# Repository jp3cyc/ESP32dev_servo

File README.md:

# ESP32dev_servo
 esp32 and neopixcel

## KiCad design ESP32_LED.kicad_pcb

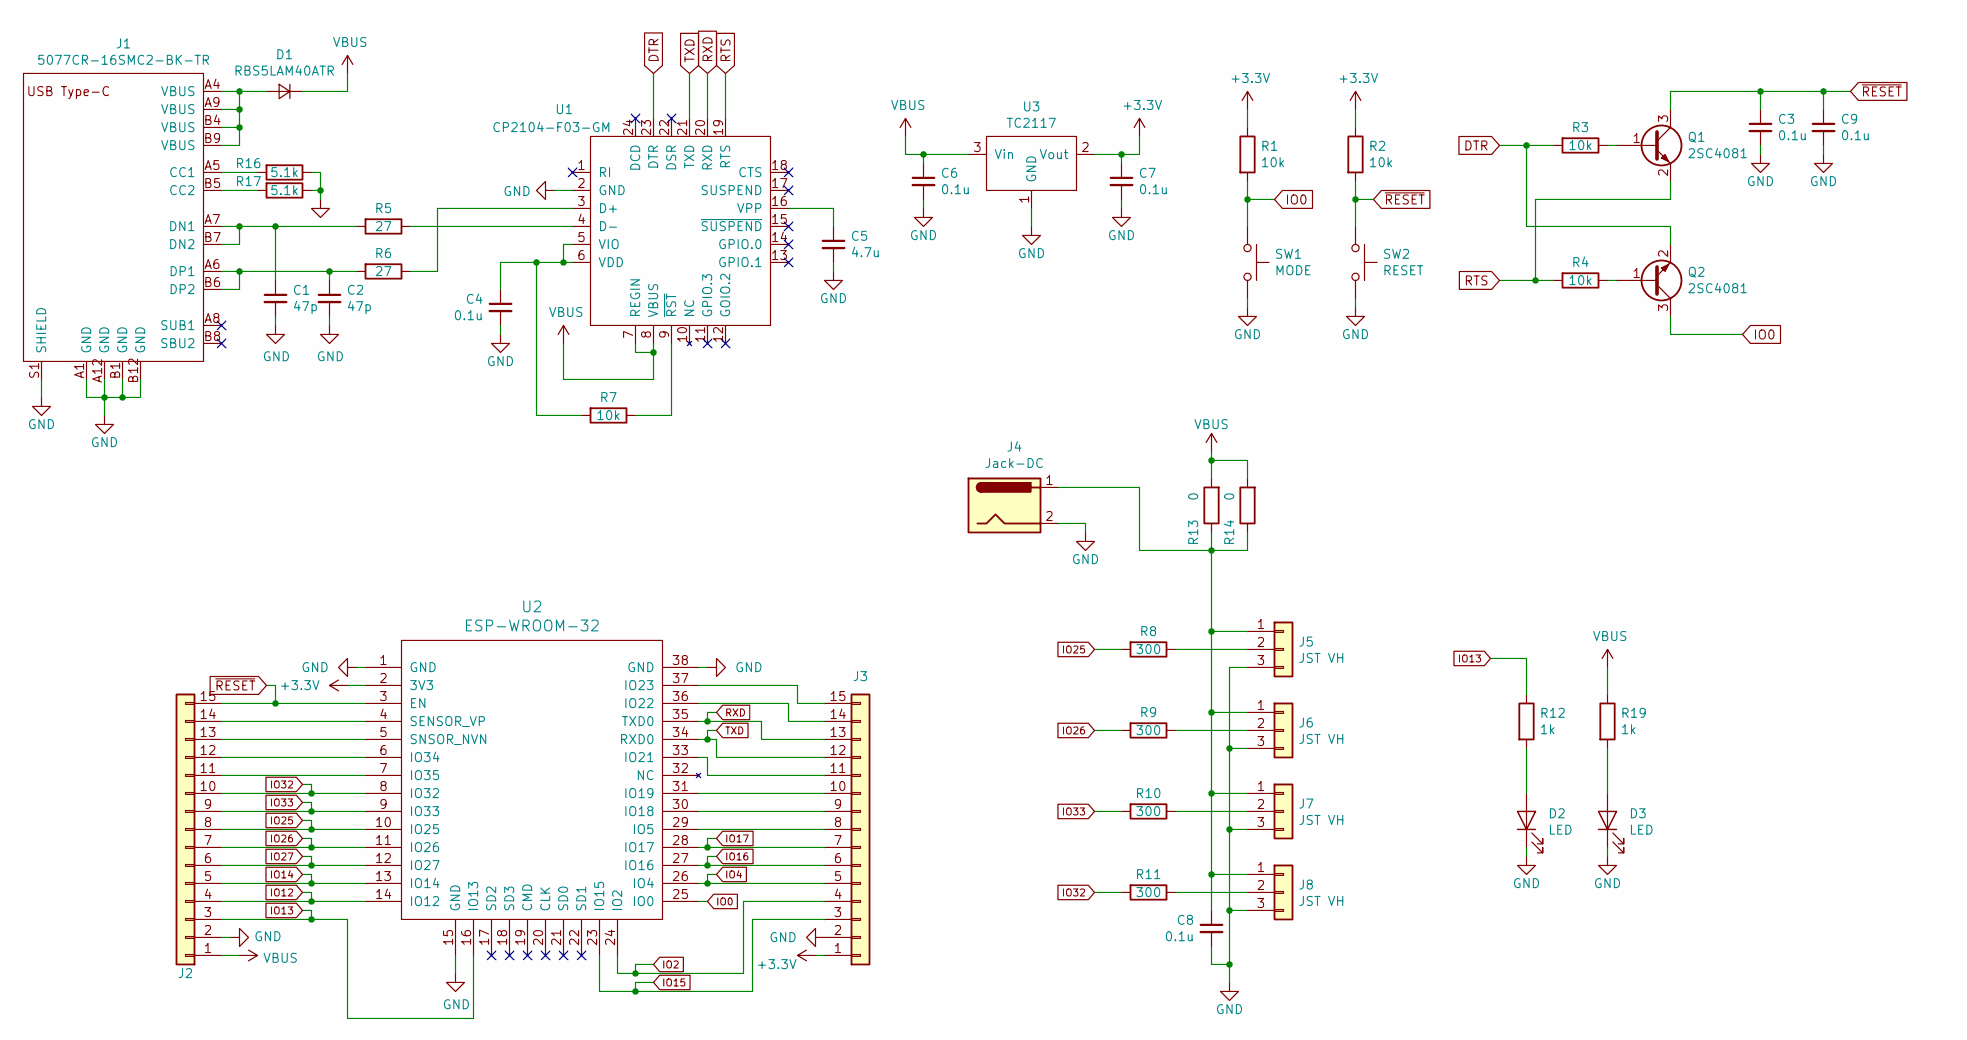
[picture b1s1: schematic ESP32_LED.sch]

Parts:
C1, C2: 47p; C_0402_1005Metric
C3, C4, C6, C7, C8, C9: 0.1u; C_0402_1005Metric
C5: 4.7u; C_0603_1608Metric
D1: RBS5LAM40ATR; SOD-128
D2, D3: LED; LED_0402_1005Metric
J1: 5077CR-16SMC2-BK-TR
J2, J3: Conn_01x15; PinHeader_1x15_P2.54mm_Vertical
J4: Jack-DC; 2DC-G213-D42
J5, J6, J7, J8: JST VH; JST_VH_B3P-VH-B_1x03_P3.96mm_Vertical
Q1, Q2: 2SC4081; SOT-323_SC-70
R1, R2, R3, R4, R7: 10k; R_0402_1005Metric
R5, R6: 27; R_0402_1005Metric
R8, R9, R10, R11: 300; R_0402_1005Metric
R12, R19: 1k; R_0402_1005Metric
R13, R14: 0; R_0805_2012Metric
R16, R17: 5.1k; R_0402_1005Metric
SW1: MODE; SKRPACE010
SW2: RESET; SKRPACE010
U1: CP2104-F03-GM; QFN-24-1EP_4x4mm_P0.5mm_EP2.7x2.7mm_ThermalVias
U2: ESP-WROOM-32; ESP32
U3: TC2117; SOT-223

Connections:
+3V3: C7.1, J3.1, R1.1, R2.1, U2.2 (3V3), U3.2 (Vout)
DTR: Q2.2 (E), R3.2, U1.23 (DTR)
GND: C1.2, C2.2, C3.2, C4.2, C5.2, C6.2, C7.2, C8.2, C9.2, D2.1 (K), D3.1 (K), J1.A1 (GND), J1.A12 (GND), J1.B1 (GND), J1.B12 (GND), J1.S1 (SHIELD), J2.2, J3.2, J4.2, J5.3, J6.3, J7.3, J8.3, R16.1, R17.1, SW1.2, SW2.2, U1.2 (GND), U2.1 (GND), U2.15 (GND), U2.38 (GND), U2.GND, U3.1 (GND)
IO0: Q2.3 (C), R1.2, SW1.1, U2.25 (IO0)
IO2: J3.4, U2.24 (IO2)
IO4: J3.5, U2.26 (IO4)
IO12: J2.4, U2.14 (IO12)
IO13: J2.3, R12.1, U2.16 (IO13)
IO14: J2.5, U2.13 (IO14)
IO15: J3.3, U2.23 (IO15)
IO16: J3.6, U2.27 (IO16)
IO17: J3.7, U2.28 (IO17)
IO25: J2.8, R8.2, U2.10 (IO25)
IO26: J2.7, R9.2, U2.11 (IO26)
IO27: J2.6, U2.12 (IO27)
IO32: J2.10, R11.2, U2.8 (IO32)
IO33: J2.9, R10.2, U2.9 (IO33)
unnamed: C1.1, J1.A7 (DN1), J1.B7 (DN2), R5.2
unnamed: C2.1, J1.A6 (DP1), J1.B6 (DP2), R6.2
unnamed: C4.1, R7.2, U1.5 (VIO), U1.6 (VDD)
unnamed: C5.1, U1.16 (VPP)
unnamed: C8.1, J4.1, J5.1, J6.1, J7.1, J8.1, R13.1, R14.1
unnamed: D1.2 (A), J1.A4 (VBUS), J1.A9 (VBUS), J1.B4 (VBUS), J1.B9 (VBUS)
unnamed: D2.2 (A), R12.2
unnamed: D3.2 (A), R19.2
unnamed: J1.A5 (CC1), R16.2
unnamed: J1.B5 (CC2), R17.2
unnamed: J2.11, U2.7 (IO35)
unnamed: J2.12, U2.6 (IO34)
unnamed: J2.13, U2.5 (SNSOR_NVN)
unnamed: J2.14, U2.4 (SENSOR_VP)
unnamed: J3.8, U2.29 (IO5)
unnamed: J3.9, U2.30 (IO18)
unnamed: J3.10, U2.31 (IO19)
unnamed: J3.11, U2.33 (IO21)
unnamed: J3.14, U2.36 (IO22)
unnamed: J3.15, U2.37 (IO23)
unnamed: J5.2, R8.1
unnamed: J6.2, R9.1
unnamed: J7.2, R10.1
unnamed: J8.2, R11.1
unnamed: Q1.1 (B), R3.1
unnamed: Q2.1 (B), R4.1
unnamed: R5.1, U1.4 (D-)
unnamed: R6.1, U1.3 (D+)
unnamed: R7.1, U1.9 (~RST)
RTS: Q1.2 (E), R4.2, U1.19 (RTS)
RXD: J3.13, U1.20 (RXD), U2.35 (TXD0)
TXD: J3.12, U1.21 (TXD), U2.34 (RXD0)
VBUS: C6.1, D1.1 (K), J2.1, R13.2, R14.2, R19.1, U1.7 (REGIN), U1.8 (VBUS), U3.3 (Vin)
~RESET: C3.1, C9.1, J2.15, Q1.3 (C), R2.2, SW2.1, U2.3 (EN)

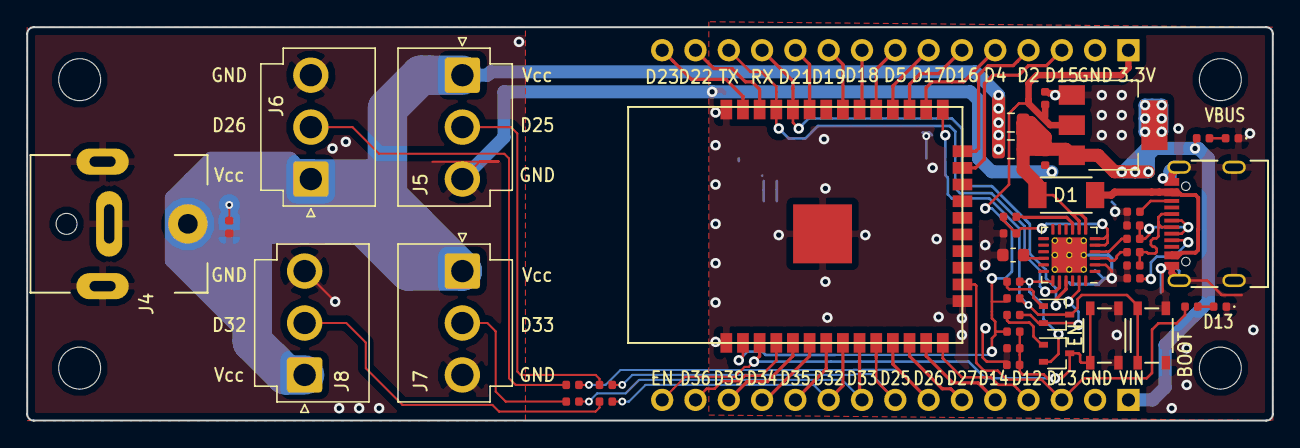
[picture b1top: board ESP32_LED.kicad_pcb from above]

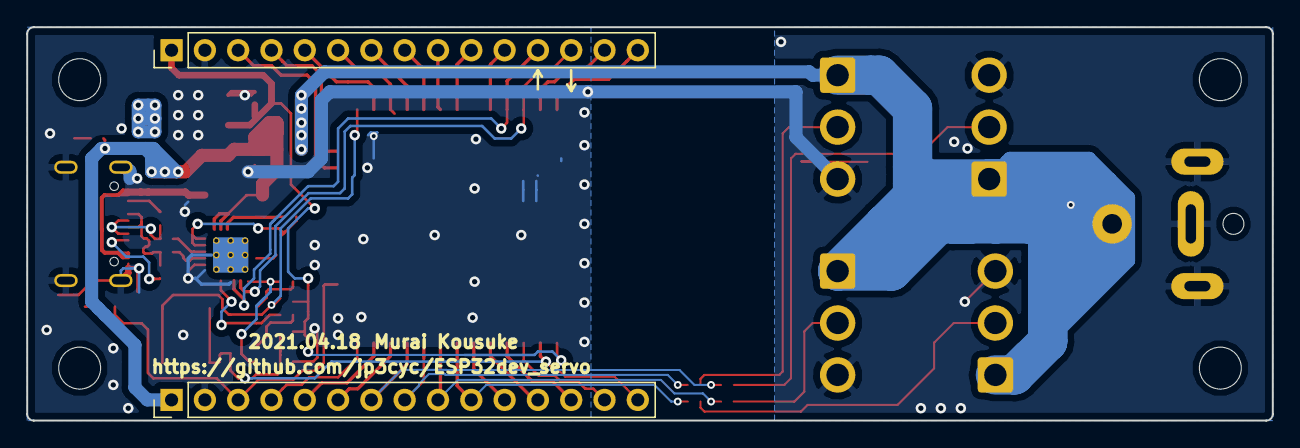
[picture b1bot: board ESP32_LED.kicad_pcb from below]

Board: 2 copper layers, 95.0 x 30.0 mm, 44 parts (2 on the bottom side), 51 nets.

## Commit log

2021-08-11 init
2021-08-11 rev1.1
2021-08-11 rev1.2
2021-08-11 rename
